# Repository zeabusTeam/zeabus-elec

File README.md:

# Zeabus-Elec
Electronic parts for Zeabus team. The design must follow these rules:
* All circuits should be compatible to __Kicad Stable Version 4.0.6__.
* USB connectors should be __Mini-USB Type B__ receptacles.
* All components, which comminicate via USB, should consume the power from their USB bus, which is 5V, with the current not more than 1A
* The USB hub must be able to provide 5V with 1A through all USB devices.
* All USB cables must be shielded.
* All communications and control buses linked between modules apart from USB and Ethernet (for example, solenoid valves control and servo signals) must be isolated with appropriate ways.

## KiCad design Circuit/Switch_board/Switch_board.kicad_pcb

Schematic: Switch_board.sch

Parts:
C1: 1uF; C_0603_HandSoldering
C2: 0.1uF; C_0603_HandSoldering
D1: BZT52C12S; D_SOD-323_HandSoldering
D2: 1PS76SB10; D_SOD-323_HandSoldering
D3: LED_PWR; LED_0603_HandSoldering
D4: LED_HALL_SENSOR_OUT; LED_0603_HandSoldering
D5: LED_IS_SWITCH_HIGH; LED_0603_HandSoldering
J1: switch_mode; Pin_Header_Straight_1x03_Pitch2.54mm
J2: switch_connector; 90136-1202
P1: power_in; XT30
Q1, Q2, Q3, Q4: 2N7002; SOT-23_Handsoldering
R1, R4: 10k; R_0603_HandSoldering
R2, R5: 1M; R_0603_HandSoldering
R3, R6, R10, R12: 1k; R_0603_HandSoldering
R7: 2.2k; R_0603_HandSoldering
R8, R9, R11: 4.7k; R_0603_HandSoldering
U1: DRV5023; SOT-23_Handsoldering

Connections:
+switch: D2.1 (K), J2.1, Q4.3 (D), R12.2
GND: C1.2, C2.2, D1.2 (A), D3.1 (K), J2.2, P1.2, Q1.2 (S), Q2.2 (S), Q3.2 (S), Q4.2 (S), R2.2, R5.2, U1.3 (GND); also elsewhere on the board
unnamed 2: C1.1, U1.1 (VCC); also elsewhere on the board
unnamed: D1.1 (K), D2.2 (A), R7.1
unnamed: D3.2 (A), R8.1
unnamed: D4.1 (K), Q1.3 (D)
unnamed: D4.2 (A), R9.1
unnamed: D5.1 (K), Q2.3 (D)
unnamed: D5.2 (A), R11.1
unnamed: J1.1, R2.1, R3.1
unnamed: J1.3, Q3.3 (D), R4.2, R5.1, R6.1
unnamed 12: P1.1; also elsewhere on the board
unnamed: Q1.1 (G), R10.1
unnamed: Q2.1 (G), R12.1
unnamed: Q3.1 (G), R3.2
unnamed: Q4.1 (G), R6.2
VCC: R1.1, R4.1, R7.2, R8.2, R9.2, R11.2; also elsewhere on the board
hall_sensor_out: C2.1, J1.2, R1.2, R10.2, U1.2 (OUT)

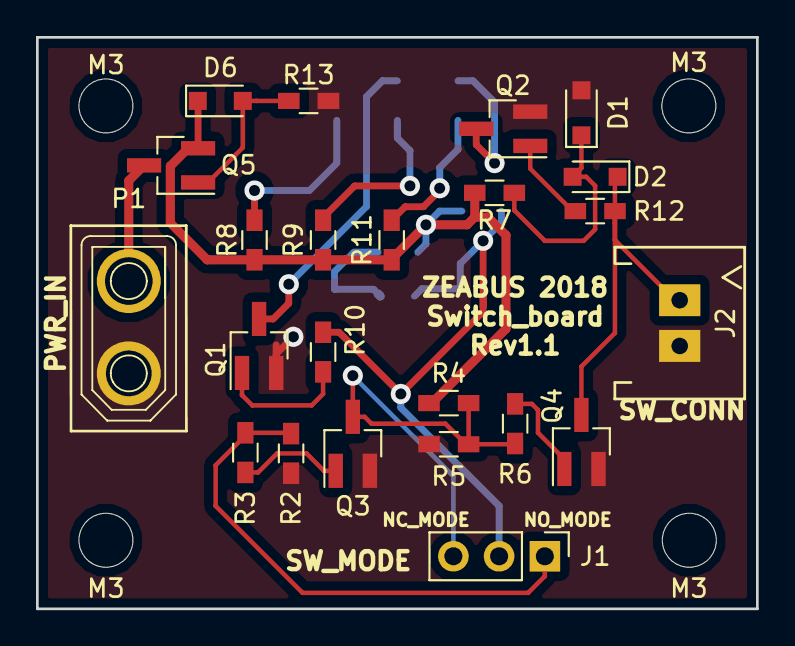
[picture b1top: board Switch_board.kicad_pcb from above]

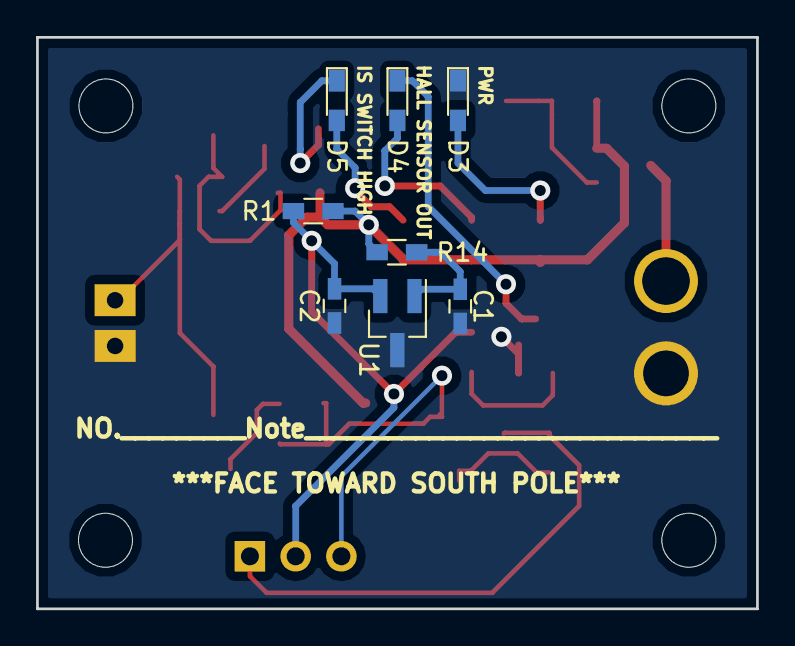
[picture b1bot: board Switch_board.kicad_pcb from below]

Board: 2 copper layers, 40.0 x 31.7 mm, 35 parts (8 on the bottom side), 19 nets.

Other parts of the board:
D6: BZT52C12S; D_SOD-323_HandSoldering
M3, M3#2, M3#3, M3#4: MountingHole_3mm
Q5: RSC002P03; SOT-23_Handsoldering
R13: 10k; R_0603_HandSoldering
R14: 100; R_0603_HandSoldering

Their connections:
GND: R13.2; also elsewhere on the board
unnamed 2: R14.1; also elsewhere on the board
unnamed: D6.2, Q5.1, R13.1
unnamed 12: Q5.3; also elsewhere on the board
VCC: D6.1, Q5.2, R14.2; also elsewhere on the board

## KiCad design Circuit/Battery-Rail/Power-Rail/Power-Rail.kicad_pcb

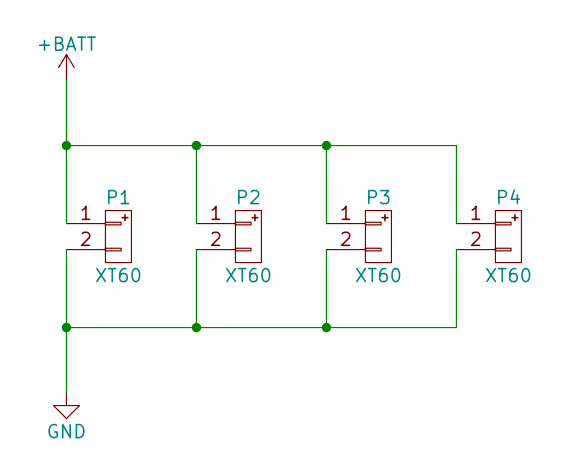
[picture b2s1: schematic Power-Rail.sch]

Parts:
P1, P2, P3, P4: XT60

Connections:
+BATT: P1.1, P2.1, P3.1, P4.1
GND: P1.2, P2.2, P3.2, P4.2

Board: 2 copper layers, 4 parts (0 on the bottom side), 2 nets, no tracks yet.

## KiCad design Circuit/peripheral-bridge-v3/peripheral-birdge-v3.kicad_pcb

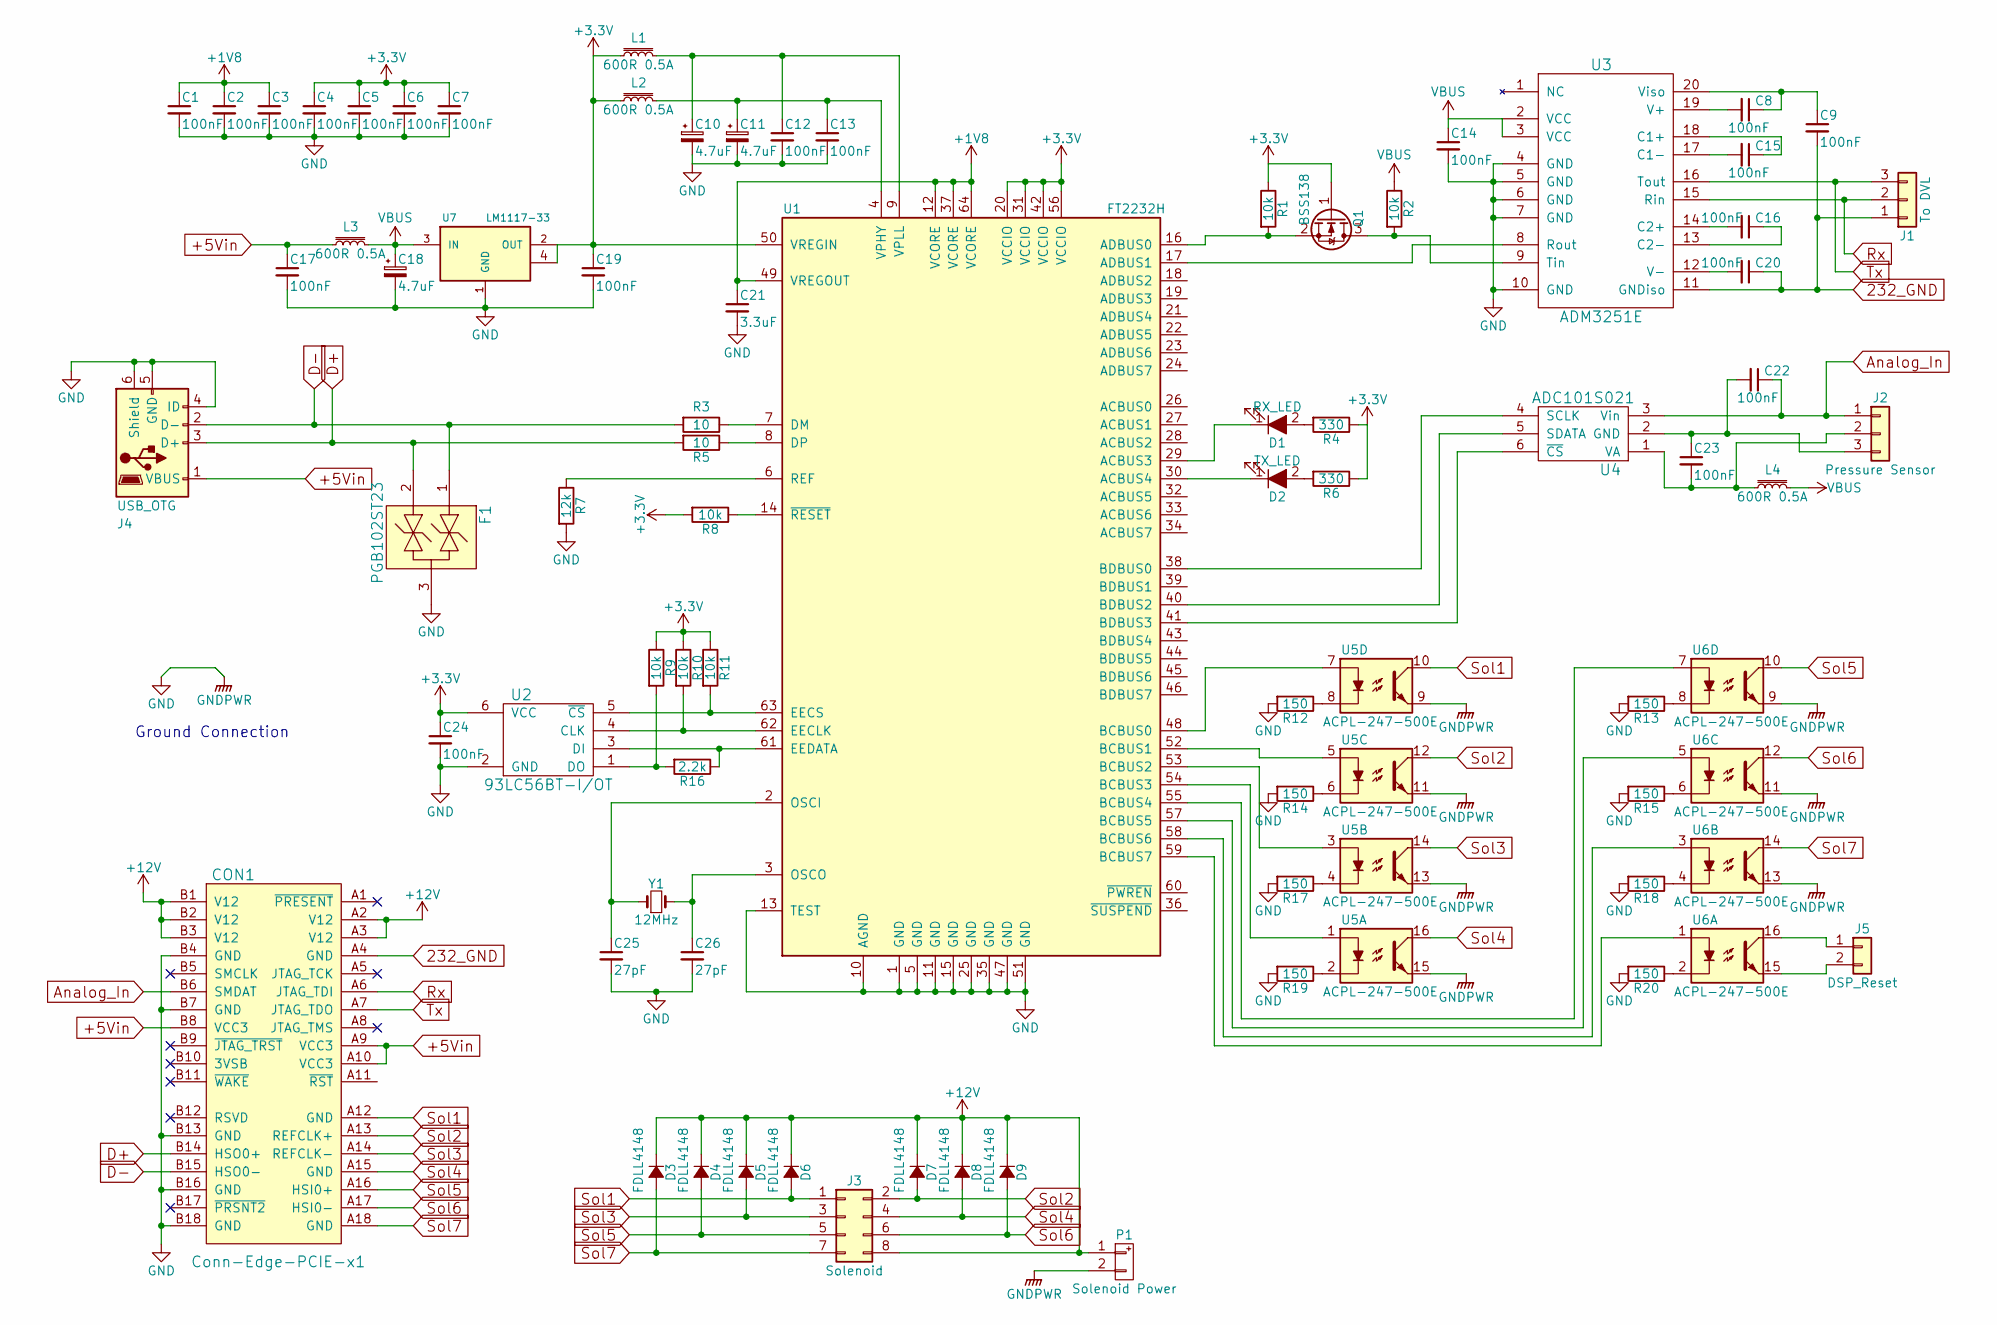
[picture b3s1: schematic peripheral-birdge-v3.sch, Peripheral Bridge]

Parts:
C1, C2, C3, C4, C5, C6, C7, C8, C9, C12, C13, C14, C15, C16, C17, C19, C20, C22, C23, C24: 100nF; C_0603
C10, C11, C18: 4.7uF; C_0805
C21: 3.3uF; C_0805
C25, C26: 27pF; C_0603
CON1: Conn-Edge-PCIE-x1; pcie-x1-edge
D1: RX_LED; LED_0603
D2: TX_LED; LED_0603
D3, D4, D5, D6, D7, D8, D9: FDLL4148; SOD-80
F1: PGB102ST23; SOT-23
J1: To DVL; 90136-2013
J2: Pressure Sensor; 90136-2013
J3: Solenoid; Pin_Header_Straight_2x04
J4: USB_OTG; USB_Mini-B
J5: DSP_Reset; Pin_Header_Straight_1x02_Pitch2.54mm
L1, L2, L3, L4: 600R 0.5A; C_0805
P1: Solenoid Power; XT60
Q1: BSS138; SOT-23
R1, R2, R8, R9, R10, R11: 10k; R_0603
R3, R5: 10; R_0603
R4, R6: 330; R_0603
R7: 12k; R_0603
R12, R13, R14, R15, R17, R18, R19, R20: 150; R_0603
R16: 2.2k; R_0603
U1: FT2232H; LQFP-64_10x10mm_Pitch0.5mm
U2: 93LC56BT-I/OT; SOT-23-6
U3: ADM3251E; SOIC-20W_7.5x12.8mm_Pitch1.27mm
U4: ADC101S021; SOT-23-6
U5, U6: ACPL-247-500E; SO16_4.4x10.3mm_Pitch1.27mm
U7: LM1117-33; SOT-223
Y1: 12MHz; Crystal_FOX-FE_SMD

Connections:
232_GND: C9.2, C20.1, CON1.A4 (GND), J1.1, U3.11 (GNDiso)
+1V8: C1.1, C2.1, C3.1, C21.1, U1.12 (VCORE), U1.37 (VCORE), U1.49 (VREGOUT), U1.64 (VCORE)
+3V3: C4.1, C5.1, C6.1, C7.1, C19.1, C24.1, L1.1, L2.1, Q1.1 (G), R1.1, R4.1, R6.1, R8.2, R9.1, R10.1, R11.1, U1.20 (VCCIO), U1.31 (VCCIO), U1.42 (VCCIO), U1.50 (VREGIN), U1.56 (VCCIO), U2.6 (VCC), U7.2 (OUT), U7.4
+5Vin: C17.1, CON1.A9 (VCC3), CON1.A10 (VCC3), CON1.B8 (VCC3), J4.1 (VBUS), L3.1
+12V: CON1.A2 (V12), CON1.A3 (V12), CON1.B1 (V12), CON1.B2 (V12), CON1.B3 (V12), D3.1 (K), D4.1 (K), D5.1 (K), D6.1 (K), D7.1 (K), D8.1 (K), D9.1 (K), J3.8, P1.1
Analog_In: C22.1, CON1.B6 (SMDAT), J2.1, U4.3 (Vin)
D+: CON1.B14 (HSO0+), F1.2, J4.3 (D+), R5.2
D-: CON1.B15 (HSO0-), F1.1, J4.2 (D-), R3.2
unnamed: C8.1, C9.1, U3.20 (Viso)
unnamed: C8.2, U3.19 (V+)
unnamed: C10.1, C12.1, L1.2, U1.9 (VPLL)
unnamed: C11.1, C13.1, L2.2, U1.4 (VPHY)
unnamed: C15.1, U3.18 (C1+)
unnamed: C15.2, U3.17 (C1-)
unnamed: C16.1, U3.13 (C2-)
unnamed: C16.2, U3.14 (C2+)
unnamed: C20.2, U3.12 (V-)
unnamed: C23.2, J2.2, L4.1, U4.1 (VA)
unnamed: C25.1, U1.2 (OSCI), Y1.1
unnamed: C26.1, U1.3 (OSCO), Y1.2
unnamed: D1.1 (K), U1.29 (ACBUS3)
unnamed: D1.2 (A), R4.2
unnamed: D2.1 (K), U1.30 (ACBUS4)
unnamed: D2.2 (A), R6.2
unnamed: J5.1, U6.16
unnamed: J5.2, U6.15
unnamed: Q1.2 (S), R1.2, U1.16 (ADBUS0)
unnamed: Q1.3 (D), R2.2, U3.9 (Tin)
unnamed: R3.1, U1.7 (DM)
unnamed: R5.1, U1.8 (DP)
unnamed: R7.1, U1.6 (REF)
unnamed: R8.1, U1.14 (~RESET)
unnamed: R10.2, U1.62 (EECLK), U2.4 (CLK)
unnamed: R11.2, U1.63 (EECS), U2.5 (~CS)
unnamed: R12.1, U5.8
unnamed: R13.1, U6.8
unnamed: R14.1, U5.6
unnamed: R15.1, U6.6
unnamed: R16.1, U1.61 (EEDATA), U2.3 (DI)
unnamed: R9.2, R16.2, U2.1 (DO)
unnamed: R17.1, U5.4
unnamed: R18.1, U6.4
unnamed: R19.1, U5.2
unnamed: R20.1, U6.2
unnamed: U1.17 (ADBUS1), U3.8 (Rout)
unnamed: U1.38 (BDBUS0), U4.4 (SCLK)
unnamed: U1.40 (BDBUS2), U4.5 (SDATA)
unnamed: U1.41 (BDBUS3), U4.6 (~CS)
unnamed: U1.48 (BCBUS0), U5.7
unnamed: U1.52 (BCBUS1), U5.5
unnamed: U1.53 (BCBUS2), U5.3
unnamed: U1.54 (BCBUS3), U5.1
unnamed: U1.55 (BCBUS4), U6.7
unnamed: U1.57 (BCBUS5), U6.5
unnamed: U1.58 (BCBUS6), U6.3
unnamed: U1.59 (BCBUS7), U6.1
Rx: CON1.A6 (JTAG_TDI), J1.2, U3.15 (Rin)
Sol1: CON1.A12 (GND), D6.2 (A), J3.1, U5.10
Sol2: CON1.A13 (REFCLK+), D7.2 (A), J3.2, U5.12
Sol3: CON1.A14 (REFCLK-), D5.2 (A), J3.3, U5.14
Sol4: CON1.A15 (GND), D8.2 (A), J3.4, U5.16
Sol5: CON1.A16 (HSI0+), D4.2 (A), J3.5, U6.10
Sol6: CON1.A17 (HSI0-), D9.2 (A), J3.6, U6.12
Sol7: CON1.A18 (GND), D3.2 (A), J3.7, U6.14
Tx: CON1.A7 (JTAG_TDO), J1.3, U3.16 (Tout)
VBUS: C14.1, C18.1, L3.2, L4.2, R2.1, U3.2 (VCC), U3.3 (VCC), U7.3 (IN)

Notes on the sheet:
Ground Connection

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
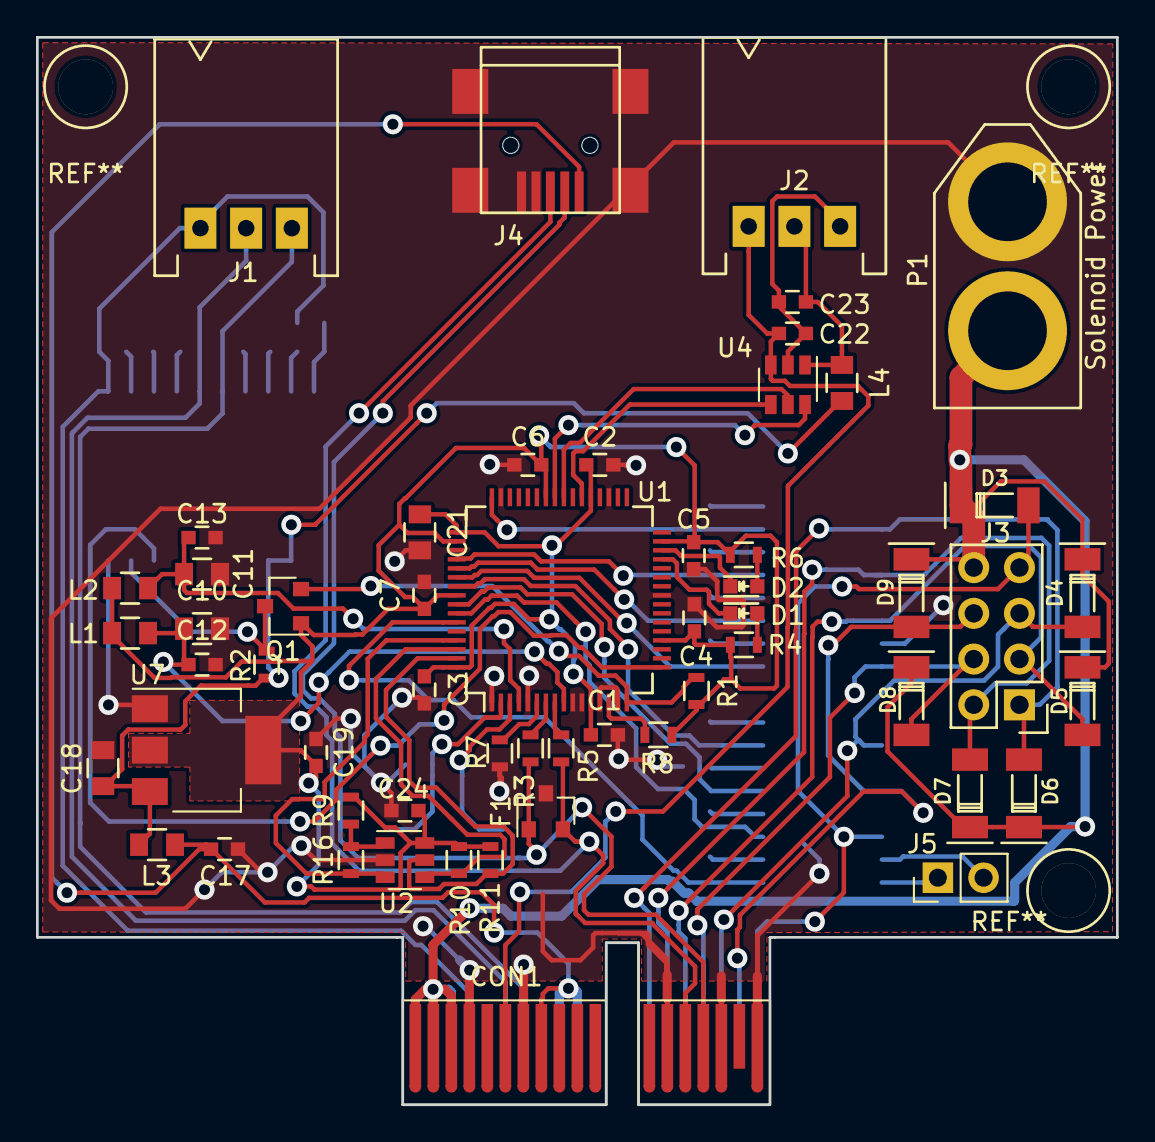
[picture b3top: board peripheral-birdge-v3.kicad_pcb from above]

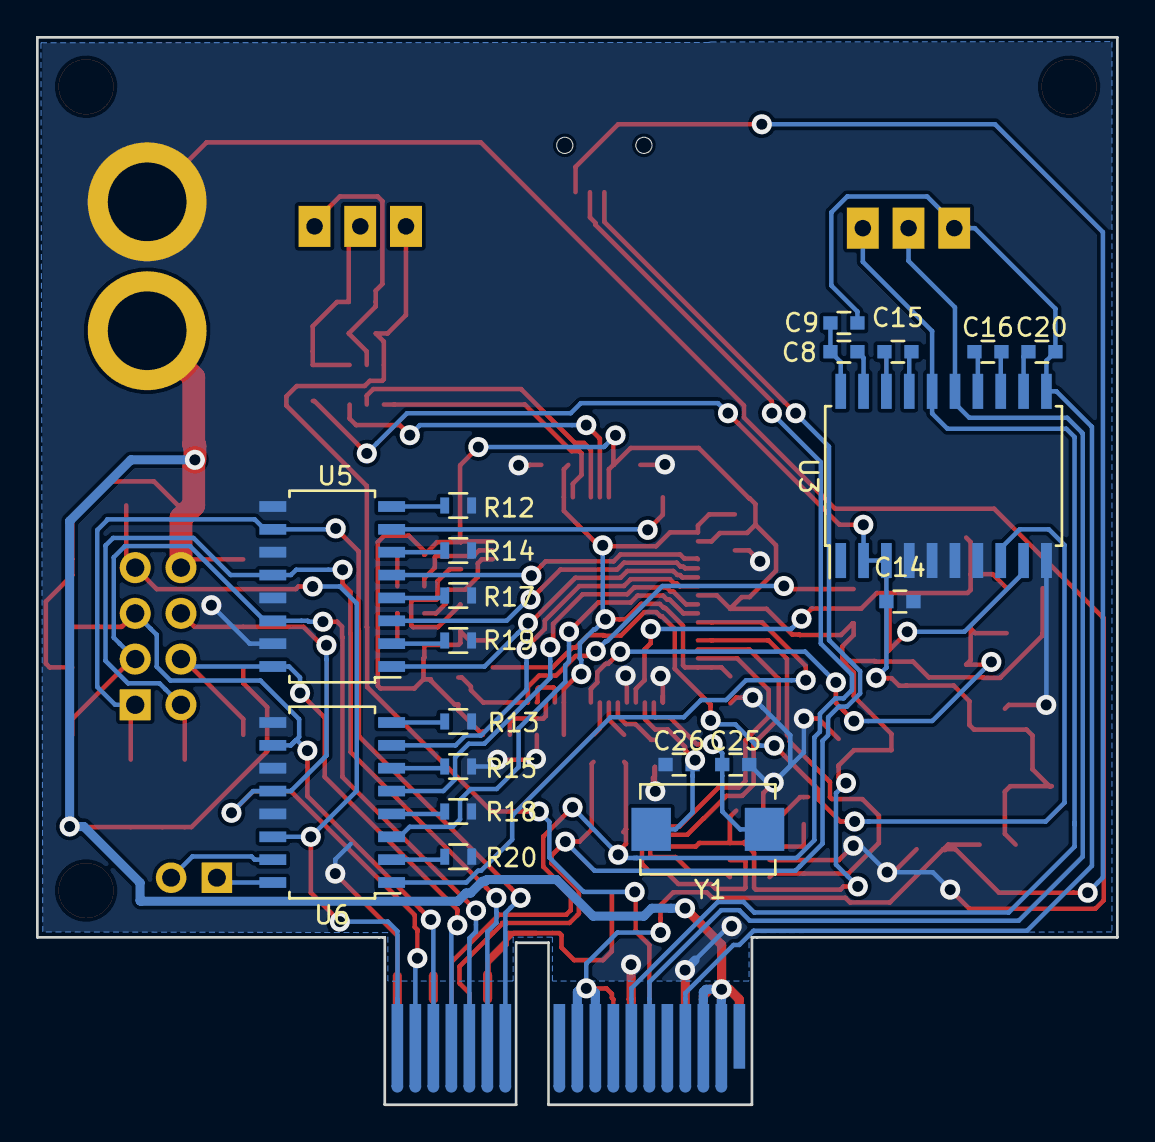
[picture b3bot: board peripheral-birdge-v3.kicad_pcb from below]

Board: 2 copper layers, 60.0 x 59.3 mm, 76 parts (20 on the bottom side), 67 nets.

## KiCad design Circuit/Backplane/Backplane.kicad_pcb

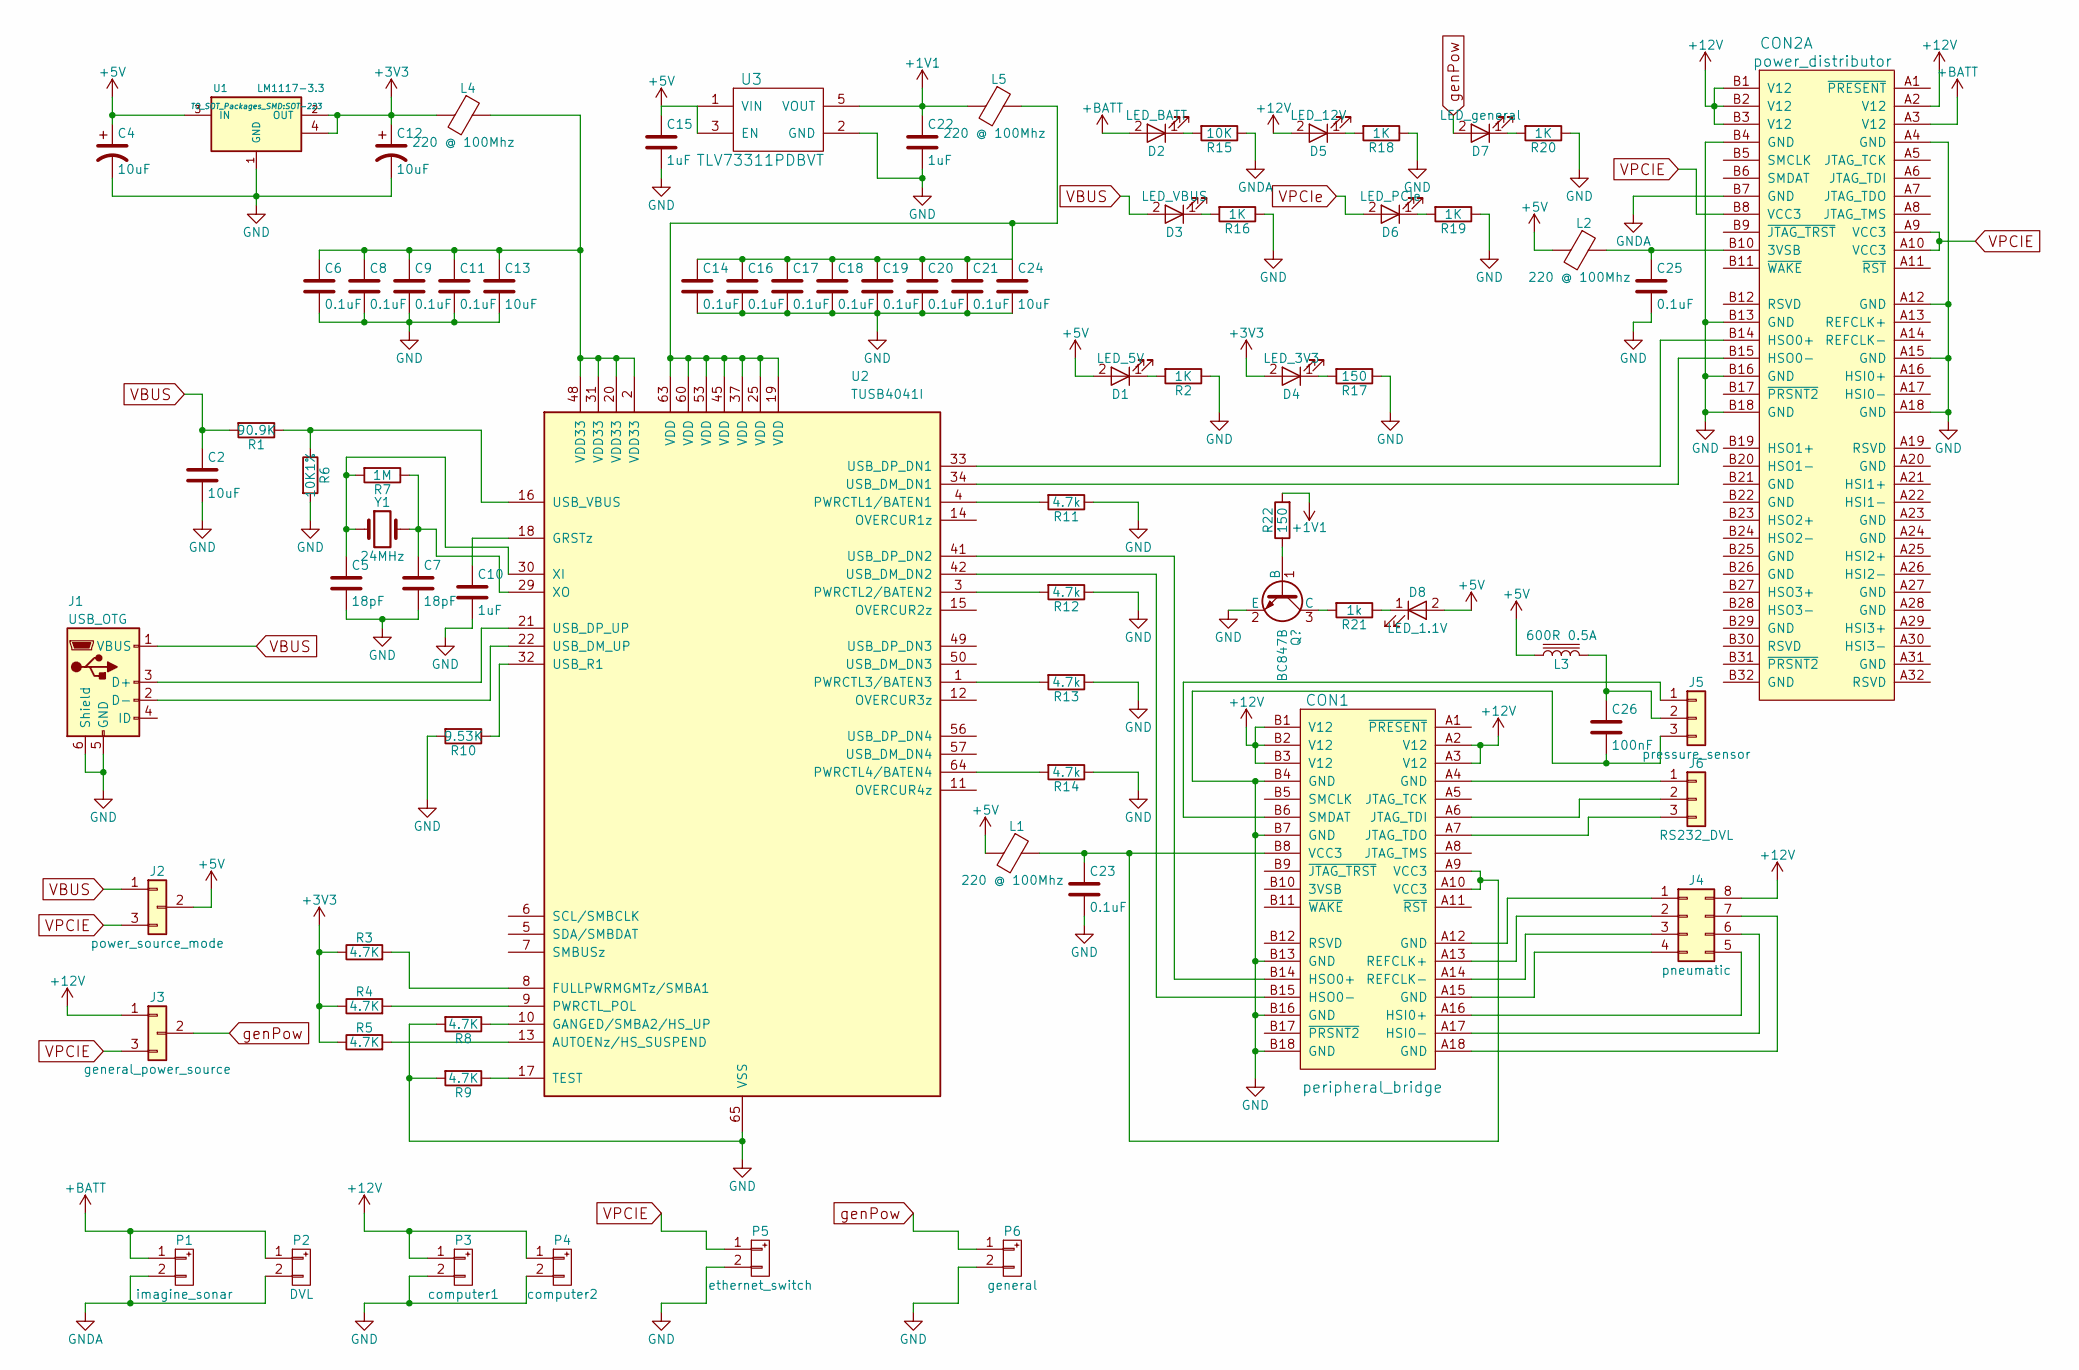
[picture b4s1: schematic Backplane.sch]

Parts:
C2, C4, C12, C13, C24: 10uF; C_0603_HandSoldering
C5, C7: 18pF; C_0603_HandSoldering
C6, C8, C9, C11, C14, C16, C17, C18, C19, C20, C21, C23, C25: 0.1uF; C_0603_HandSoldering
C10, C15, C22: 1uF; C_0603_HandSoldering
C26: 100nF; C_0603_HandSoldering
CON1: peripheral_bridge; pcie-x1-conn
CON2: power_distributor; pcie-x16-conn
D1: LED_5V; LED_0603_HandSoldering
D2: LED_BATT; LED_0603_HandSoldering
D3: LED_VBUS; LED_0603_HandSoldering
D4: LED_3V3; LED_0603_HandSoldering
D5: LED_12V; LED_0603_HandSoldering
D6: LED_PCIe; LED_0603_HandSoldering
D7: LED_general; LED_0603_HandSoldering
D8: LED_1.1V; LED_0603_HandSoldering
J1: USB_OTG; USB_Mini-B
J2: power_source_mode; Pin_Header_Straight_1x03_Pitch2.54mm
J3: general_power_source; Pin_Header_Straight_1x03_Pitch2.54mm
J4: pneumatic; Pin_Header_Straight_2x04
J5: pressure_sensor; 70543-0002
J6: RS232_DVL; 70543-0002
L1, L2, L4, L5: 220 @ 100Mhz; C_0603_HandSoldering
L3: 600R 0.5A; C_0805_HandSoldering
P1: imagine_sonar; XT30
P2: DVL; XT30
P3: computer1; XT30
P4: computer2; XT30
P5: ethernet_switch; XT30
P6: general; XT30
R1: 90.9K; R_0603_HandSoldering
R2, R16, R18, R19, R20: 1K; R_0603_HandSoldering
R3, R4, R5, R8, R9: 4.7K; R_0603_HandSoldering
R6: 10K1%; R_0603_HandSoldering
R7: 1M; R_0603_HandSoldering
R10: 9.53K; R_0603_HandSoldering
R11, R12, R13, R14: 4.7k; R_0603_HandSoldering
R15: 10K; R_0603_HandSoldering
R17, R22: 150; R_0603_HandSoldering
R21: 1k; R_0603_HandSoldering
U1: LM1117-3.3; SOT-223
U2: TUSB4041I; HTQFP-64-1EP_10x10mm_Pitch0.5mm_ThermalPad
U3: TLV73311PDBVT; SOT-23-5_HandSoldering
Y1: 24MHz; Crystal_SMD_Abracon_ABM3-2pin_5.0x3.2mm_HandSoldering

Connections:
+1V1: C22.1, L5.2, R22.2, U3.5 (VOUT)
+3V3: C12.1, D4.2 (A), L4.2, R3.1, R4.1, R5.1, U1.2 (OUT), U1.4
+5V: C4.1, C15.1, D1.2 (A), D8.2 (A), J2.2, L1.2, L2.2, L3.1, U1.3 (IN), U3.1 (VIN), U3.3 (EN)
+12V: CON1.A2 (V12), CON1.A3 (V12), CON1.B1 (V12), CON1.B2 (V12), CON1.B3 (V12), CON2.A2 (V12), CON2.B1 (V12), CON2.B2 (V12), CON2.B3 (V12), D5.2 (A), J3.1, J4.8, P3.1, P4.1
+BATT: CON2.A3 (V12), D2.2 (A), P1.1, P2.1
GND: C2.2, C4.2, C5.2, C6.2, C7.2, C8.2, C9.2, C10.2, C11.2, C12.2, C13.2, C14.2, C15.2, C16.2, C17.2, C18.2, C19.2, C20.2, C21.2, C22.2, C23.2, C24.2, C25.2, C26.2, CON1.B4 (GND), CON1.B7 (GND), CON1.B13 (GND), CON1.B16 (GND), CON1.B18 (GND), CON2.A4 (GND), CON2.A12 (GND), CON2.A15 (GND), CON2.A18 (GND), CON2.B4 (GND), CON2.B13 (GND), CON2.B16 (GND), CON2.B18 (GND), J1.5 (GND), J1.6 (Shield), J5.3, P3.2, P4.2, P5.2, P6.2, R2.1, R6.2, R8.2, R9.2, R10.2, R11.1, R12.1, R13.1, R14.1, R16.1, R17.1, R18.1, R19.1, R20.1, U1.1 (GND), U2.65 (VSS), U3.2 (GND); also elsewhere on the board
GNDA: CON2.B7 (GND), P1.2, P2.2, R15.1
unnamed: C5.1, R7.2, U2.30 (XI), Y1.1
unnamed: C7.1, R7.1, U2.29 (XO), Y1.2
unnamed: C10.1, U2.18 (GRSTz)
unnamed: C6.1, C8.1, C9.1, C11.1, C13.1, L4.1, U2.2 (VDD33), U2.20 (VDD33), U2.31 (VDD33), U2.48 (VDD33)
unnamed: C14.1, C16.1, C17.1, C18.1, C19.1, C20.1, C21.1, C24.1, L5.1, U2.19 (VDD), U2.25 (VDD), U2.37 (VDD), U2.45 (VDD), U2.53 (VDD), U2.60 (VDD), U2.63 (VDD)
unnamed: C23.1, CON1.A9 (VCC3), CON1.A10 (VCC3), CON1.B8 (VCC3), L1.1
unnamed: C25.1, CON2.B10 (3VSB), L2.1
unnamed: C26.1, J5.2, L3.2
unnamed: CON1.A4 (GND), J6.1
unnamed: CON1.A6 (JTAG_TDI), J6.2
unnamed: CON1.A7 (JTAG_TDO), J6.3
unnamed: CON1.A12 (GND), J4.1
unnamed: CON1.A13 (REFCLK+), J4.2
unnamed: CON1.A14 (REFCLK-), J4.3
unnamed: CON1.A15 (GND), J4.4
unnamed: CON1.A16 (HSI0+), J4.5
unnamed: CON1.A17 (HSI0-), J4.6
unnamed: CON1.A18 (GND), J4.7
unnamed: CON1.B6 (SMDAT), J5.1
unnamed: CON1.B14 (HSO0+), U2.41 (USB_DP_DN2)
unnamed: CON1.B15 (HSO0-), U2.42 (USB_DM_DN2)
unnamed: CON2.B14 (HSO0+), U2.33 (USB_DP_DN1)
unnamed: CON2.B15 (HSO0-), U2.34 (USB_DM_DN1)
unnamed: D1.1 (K), R2.2
unnamed: D2.1 (K), R15.2
unnamed: D3.1 (K), R16.2
unnamed: D4.1 (K), R17.2
unnamed: D5.1 (K), R18.2
unnamed: D6.1 (K), R19.2
unnamed: D7.1 (K), R20.2
unnamed: D8.1 (K), R21.1
unnamed: J1.2 (D-), U2.22 (USB_DM_UP)
unnamed: J1.3 (D+), U2.21 (USB_DP_UP)
unnamed 95: R22.1; also elsewhere on the board
unnamed 96: R21.2; also elsewhere on the board
unnamed: R1.1, R6.1, U2.16 (USB_VBUS)
unnamed: R3.2, U2.8 (FULLPWRMGMTz/SMBA1)
unnamed: R4.2, U2.9 (PWRCTL_POL)
unnamed: R5.2, U2.13 (AUTOENz/HS_SUSPEND)
unnamed: R8.1, U2.10 (GANGED/SMBA2/HS_UP)
unnamed: R9.1, U2.17 (TEST)
unnamed: R10.1, U2.32 (USB_R1)
unnamed: R11.2, U2.4 (PWRCTL1/BATEN1)
unnamed: R12.2, U2.3 (PWRCTL2/BATEN2)
unnamed: R13.2, U2.1 (PWRCTL3/BATEN3)
unnamed: R14.2, U2.64 (PWRCTL4/BATEN4)
VBUS: C2.1, D3.2 (A), J1.1 (VBUS), J2.1, R1.2
VPCIE: CON2.A9 (VCC3), CON2.A10 (VCC3), CON2.B8 (VCC3), D6.2 (A), J2.3, J3.3, P5.1
genPow: D7.2 (A), J3.2, P6.1

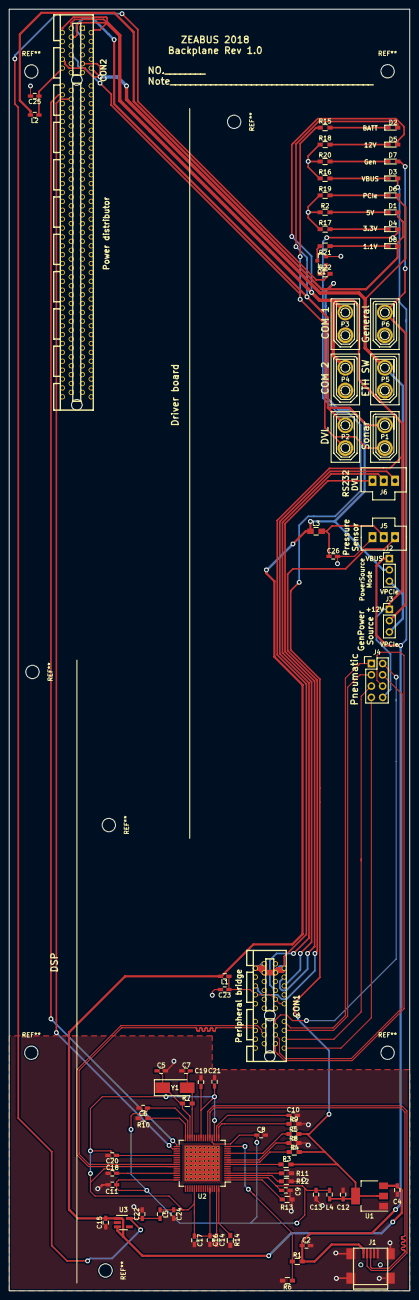
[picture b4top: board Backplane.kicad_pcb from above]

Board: 2 copper layers, 90.2 x 288.5 mm, 78 parts (0 on the bottom side), 56 nets.

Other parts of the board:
Q1: BC817-40; SOT-23

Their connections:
GND: Q1.2; also elsewhere on the board
unnamed 95: Q1.1; also elsewhere on the board
unnamed 96: Q1.3; also elsewhere on the board

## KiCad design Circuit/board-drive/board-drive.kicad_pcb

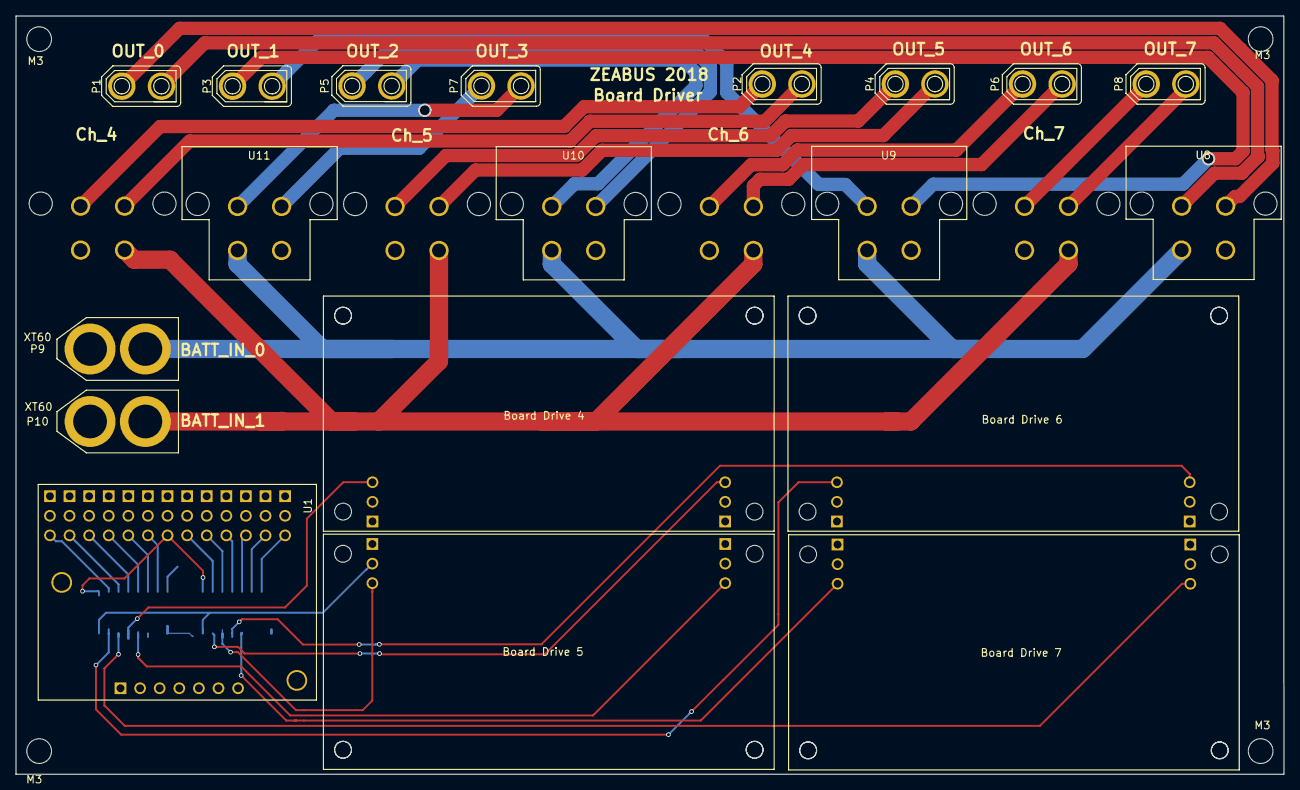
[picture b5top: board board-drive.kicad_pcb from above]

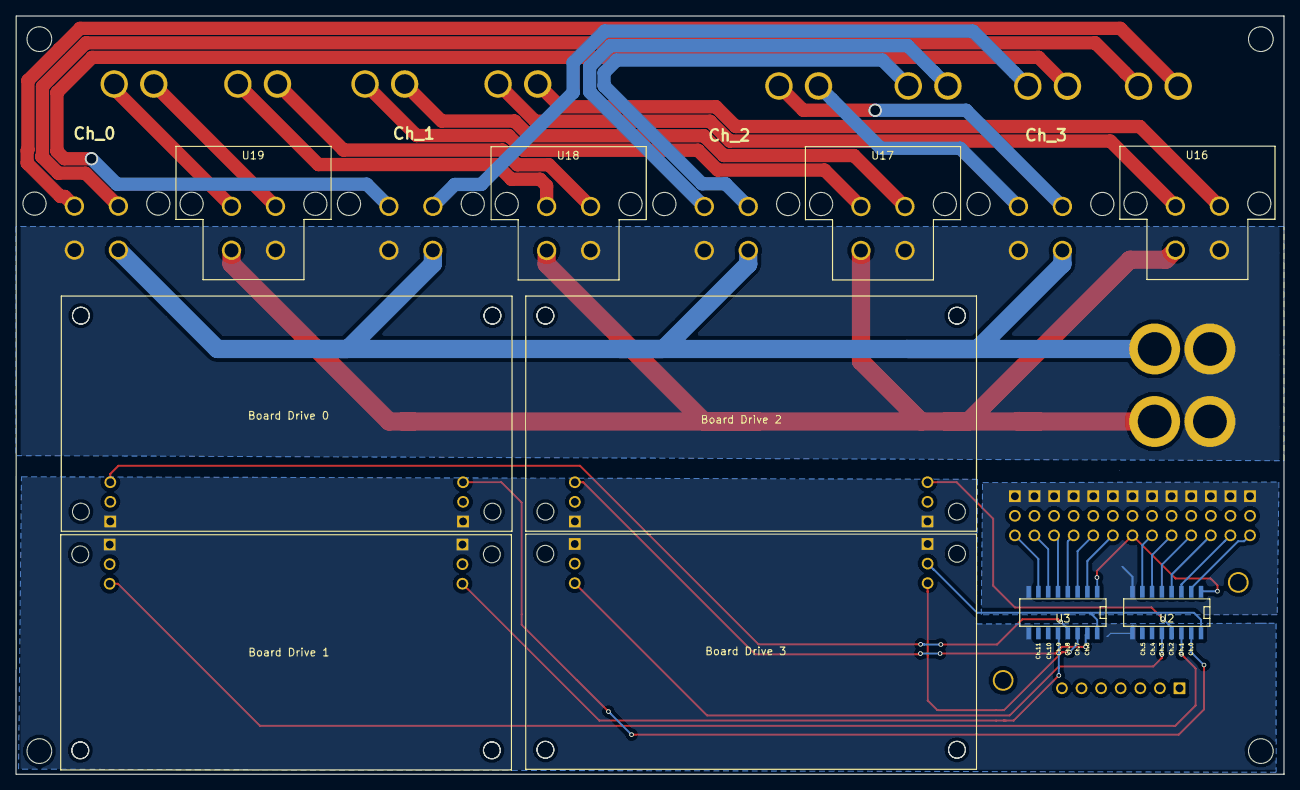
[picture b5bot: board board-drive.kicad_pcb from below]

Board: 2 copper layers, 164.3 x 98.3 mm, 33 parts (10 on the bottom side), 43 nets.

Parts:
Board Drive 0, Board Drive 1, Board Drive 2, Board Drive 3, Board Drive 4, Board Drive 5, Board Drive 6, Board Drive 7: Pololu_SimpleMotorController24v23_withnoPowerDist; pololu_motorcontroller24v23
M3, M3#2, M3#3, M3#4: MountingHole_3.2mm_M3
P1, P2, P3, P4, P5, P6, P7, P8: XT30
P9, P10: XT60
U1: Pololu_Maestro12
U2, U3: Si8660BA-B-IS1; Narrow-SOIC-16
U8, U9, U10, U11, U16, U17, U18, U19: PowerDist_WiretoBoard

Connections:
+5V: U1.3, U2.1, U3.1
/+5v_BEC: Board Drive 5.1, U2.16, U3.16
/BATTGND: P9.2, P10.2, U8.2, U9.2, U10.2, U11.2, U16.2, U17.2, U18.2, U19.2
/BATTIN_0: P9.1, U8.1, U9.1, U10.1, U11.1
/BATTIN_1: P10.1, U16.1, U17.1, U18.1, U19.1
/OUTA_0: P1.1, U8.3
/OUTA_1: P3.1, U9.3
/OUTA_2: P5.1, U10.3
/OUTA_3: P7.1, U11.3
/OUTA_4: P2.1, U16.3
/OUTA_5: P4.1, U17.3
/OUTA_6: P6.1, U18.3
/OUTA_7: P8.1, U19.3
/OUTB_0: P1.2, U8.4
/OUTB_1: P3.2, U9.4
/OUTB_2: P5.2, U10.4
/OUTB_3: P7.2, U11.4
/OUTB_4: P2.2, U16.4
/OUTB_5: P4.2, U17.4
/OUTB_6: P6.2, U18.4
/OUTB_7: P8.2, U19.4
/signal0: Board Drive 0.2, U2.15
/signal1: Board Drive 1.2, U2.14
/signal2: Board Drive 2.2, U2.13
/signal3: Board Drive 3.2, U2.12
/signal6: Board Drive 4.2, U3.15
/signal7: Board Drive 5.2, U3.14
/signal8: Board Drive 6.2, U3.13
/signal9: Board Drive 7.2, U3.12
GNDA: Board Drive 0.3, Board Drive 1.3, Board Drive 2.3, Board Drive 3.3, Board Drive 4.3, Board Drive 5.3, Board Drive 6.3, Board Drive 7.3, U2.9, U3.9
GNDD: U1.9, U1.10, U2.8, U3.8
unnamed: U1.11, U2.2
unnamed: U1.12, U2.3
unnamed: U1.13, U2.4
unnamed: U1.14, U2.5
unnamed: U1.15, U2.6
unnamed: U1.16, U2.7
unnamed: U1.17, U3.2
unnamed: U1.18, U3.3
unnamed: U1.19, U3.4
unnamed: U1.20, U3.5
unnamed: U1.21, U3.6
unnamed: U1.22, U3.7

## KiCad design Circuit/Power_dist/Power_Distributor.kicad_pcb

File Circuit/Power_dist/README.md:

# Zeabus-Elec-2017-Power_dist
## Use relative path to ../Kicad-Libraries for specific components
Power Distributor for Zeabus 2017. The circuit provides:

1. Unregulated power with a common kill-switch for all thrusters
2. Isolated regulated __5V 4A(max)__ for:
 * An Ethernet switch.
 * A USB hub, which provides power for all USB slaves.
 * *4* x Optional power socket for cameras.
3. *2* x Isolated regulated __12V 6A(max)__ for lamps. These supples must be able to switch on/off through software.
4. Isolated regulated __12V 6A(max)__ for:
 * *2* x NUC computers.
 * *7* x Solenoid valves.

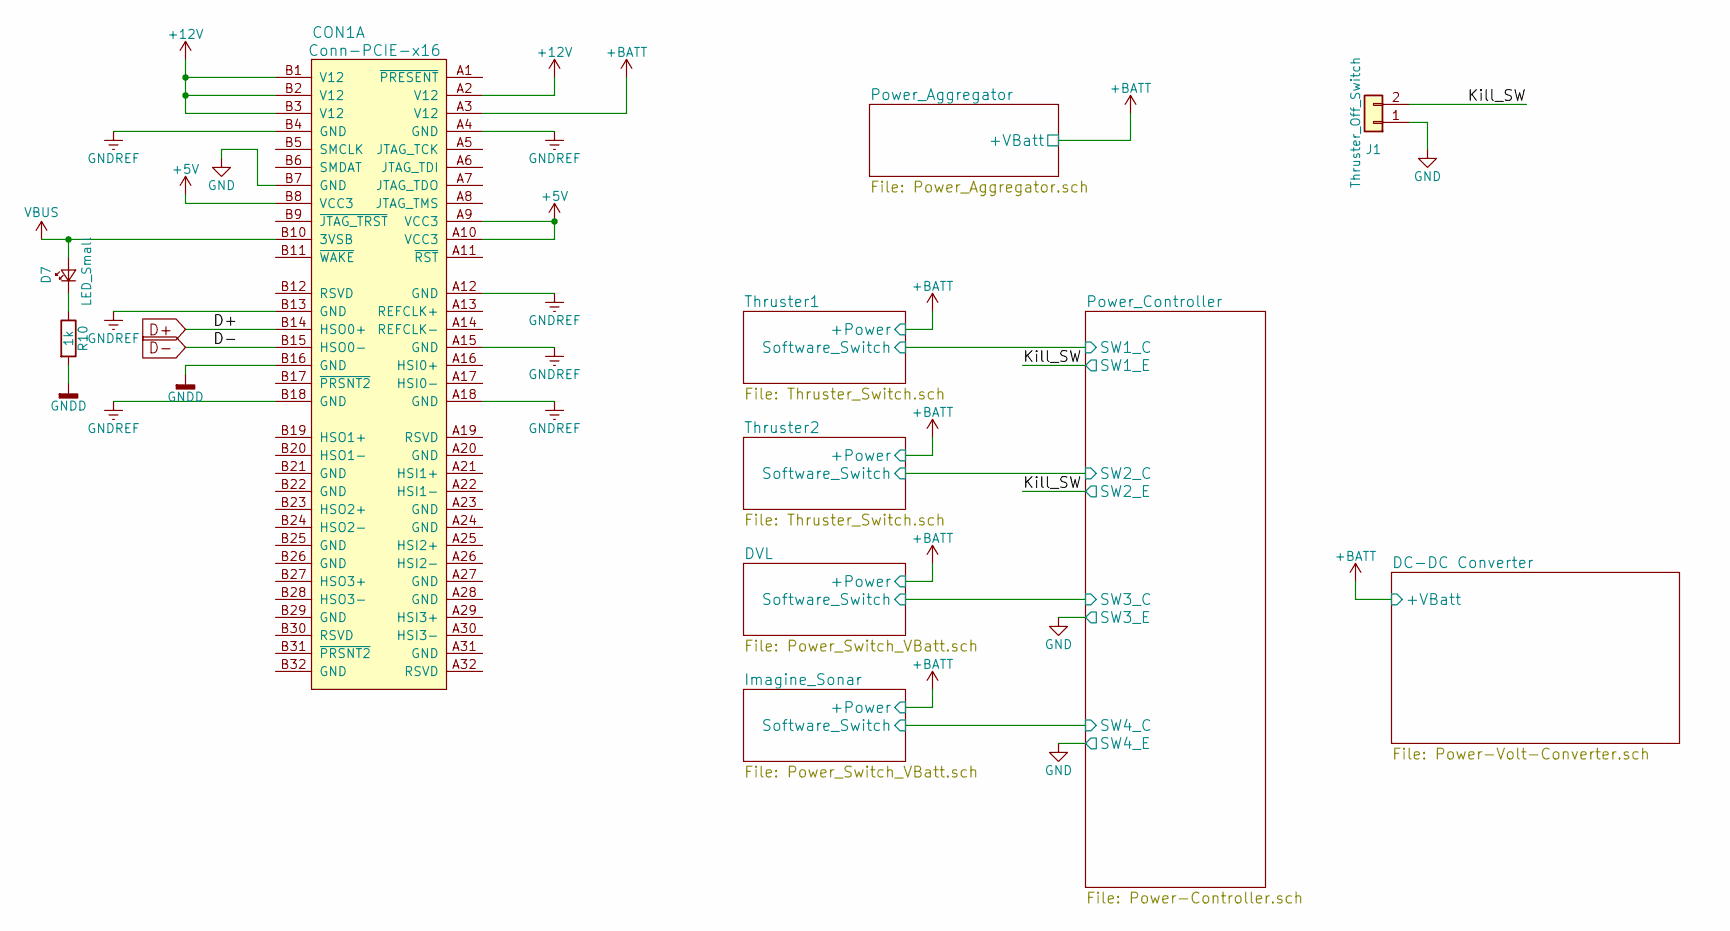
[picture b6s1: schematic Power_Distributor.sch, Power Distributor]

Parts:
CON1: Conn-PCIE-x16; pcie-x16-edge
D7: LED_Small; LED_0603_HandSoldering
J1: Thruster_Off_Switch; Pin_Header_Straight_1x02_Pitch2.54mm
R10: 1k; R_0603_HandSoldering

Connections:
+5V: CON1.A9 (VCC3), CON1.A10 (VCC3), CON1.B8 (VCC3); also elsewhere on the board
+12V: CON1.A2 (V12), CON1.B1 (V12), CON1.B2 (V12), CON1.B3 (V12); also elsewhere on the board
+BATT: CON1.A3 (V12); also elsewhere on the board
/Kill_SW: J1.2; also elsewhere on the board
D+: CON1.B14 (HSO0+); also elsewhere on the board
D-: CON1.B15 (HSO0-); also elsewhere on the board
GND: CON1.B7 (GND), J1.1; also elsewhere on the board
GNDD: CON1.B16 (GND), R10.2; also elsewhere on the board
GNDREF: CON1.A4 (GND), CON1.A12 (GND), CON1.A15 (GND), CON1.A18 (GND), CON1.B4 (GND), CON1.B13 (GND), CON1.B18 (GND); also elsewhere on the board
unnamed: D7.1 (K), R10.1
VBUS: CON1.B10 (3VSB), D7.2 (A); also elsewhere on the board
